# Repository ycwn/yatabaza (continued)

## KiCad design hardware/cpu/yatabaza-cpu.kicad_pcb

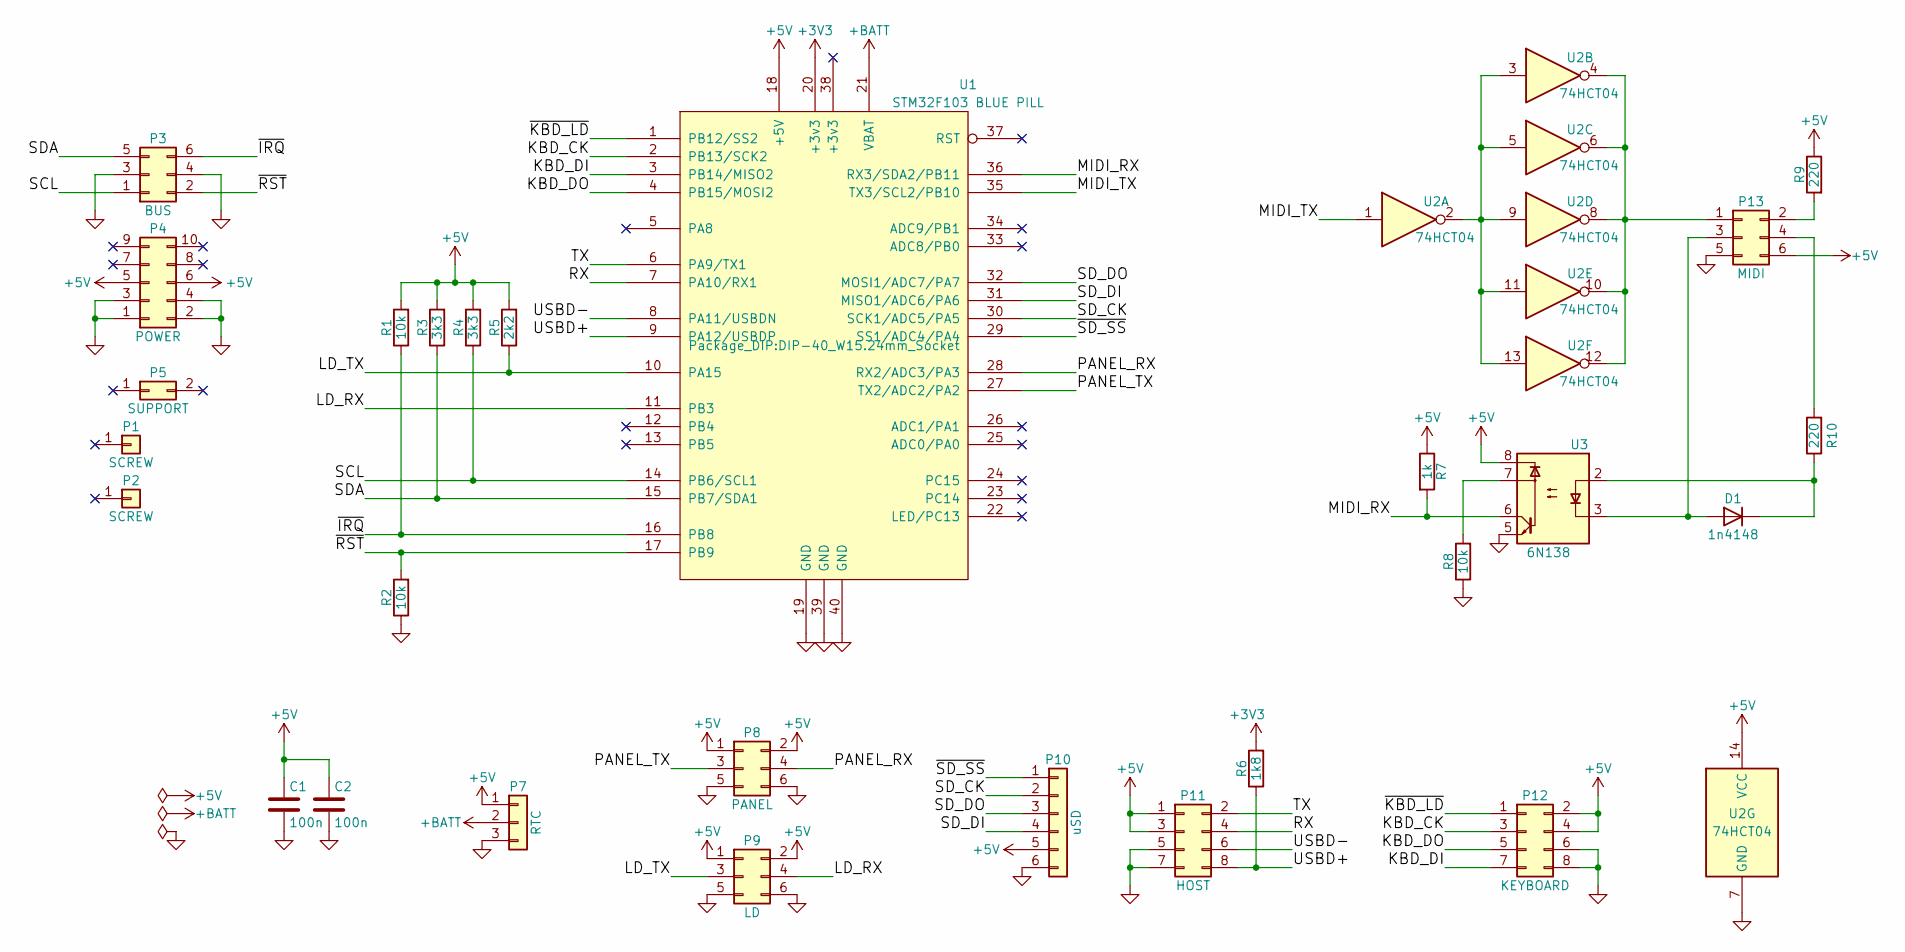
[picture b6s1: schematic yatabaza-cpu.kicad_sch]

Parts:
C1, C2: 100n; C_Disc_D3.0mm_W1.6mm_P2.50mm
D1: 1n4148; D_DO-35_SOD27_P2.54mm_Vertical_KathodeUp
P1, P2: SCREW; MountingHole_2.2mm_M2_ISO14580_Pad
P3: BUS; PinHeader_2x03_P2.54mm_Vertical
P4: POWER; PinHeader_2x05_P2.54mm_Vertical
P5: SUPPORT; PinHeader_1x02_P2.54mm_Vertical
P7: RTC; PinHeader_1x03_P2.54mm_Vertical
P8: PANEL; PinHeader_2x03_P2.54mm_Vertical
P9: LD; PinHeader_2x03_P2.54mm_Vertical
P10: uSD; PinHeader_1x06_P2.54mm_Vertical
P11: HOST; PinHeader_2x04_P2.54mm_Vertical
P12: KEYBOARD; PinHeader_2x04_P2.54mm_Horizontal
P13: MIDI; PinHeader_2x03_P2.54mm_Vertical
R1, R2, R8: 10k; R_Axial_DIN0204_L3.6mm_D1.6mm_P7.62mm_Horizontal
R3, R4: 3k3; R_Axial_DIN0204_L3.6mm_D1.6mm_P7.62mm_Horizontal
R5: 2k2; R_Axial_DIN0204_L3.6mm_D1.6mm_P2.54mm_Vertical
R6: 1k8; R_Axial_DIN0204_L3.6mm_D1.6mm_P7.62mm_Horizontal
R7: 1k; R_Axial_DIN0204_L3.6mm_D1.6mm_P7.62mm_Horizontal
R9, R10: 220; R_Axial_DIN0204_L3.6mm_D1.6mm_P2.54mm_Vertical
U1: STM32F103 BLUE PILL; DIP-40_W15.24mm_Socket
U2: 74HCT04; DIP-14_W7.62mm
U3: 6N138; DIP-8_W7.62mm

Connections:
+3V3: R6.2, U1.20 (+3v3)
+5V: C1.1, C2.1, P4.5, P4.6, P7.1, P8.1, P8.2, P9.1, P9.2, P10.5, P11.1, P11.3, P12.2, P12.4, P13.6, R1.2, R3.2, R4.2, R5.2, R7.1, R9.1, U1.18 (+5V), U2.14 (VCC), U3.8
+BATT: P7.2, U1.21 (VBAT)
/KBD_CK: P12.3, U1.2 (PB13/SCK2)
/KBD_DI: P12.7, U1.3 (PB14/MISO2)
/KBD_DO: P12.5, U1.4 (PB15/MOSI2)
/LD_RX: P9.4, U1.11 (PB3)
/LD_TX: P9.3, R5.1, U1.10 (PA15)
/MIDI_RX: R7.2, U1.36 (RX3/SDA2/PB11), U3.6
/MIDI_TX: U1.35 (TX3/SCL2/PB10), U2.1
/PANEL_RX: P8.4, U1.28 (RX2/ADC3/PA3)
/PANEL_TX: P8.3, U1.27 (TX2/ADC2/PA2)
/RX: P11.4, U1.7 (PA10/RX1)
/SCL: P3.1, R4.1, U1.14 (PB6/SCL1)
/SDA: P3.5, R3.1, U1.15 (PB7/SDA1)
/SD_CK: P10.2, U1.30 (SCK1/ADC5/PA5)
/SD_DI: P10.4, U1.31 (MISO1/ADC6/PA6)
/SD_DO: P10.3, U1.32 (MOSI1/ADC7/PA7)
/TX: P11.2, U1.6 (PA9/TX1)
/USBD+: P11.8, R6.1, U1.9 (PA12/USBDP)
/USBD-: P11.6, U1.8 (PA11/USBDN)
/~IRQ: P3.6, R1.1, U1.16 (PB8)
/~KBD_LD: P12.1, U1.1 (PB12/SS2)
/~RST: P3.2, R2.2, U1.17 (PB9)
/~SD_SS: P10.1, U1.29 (SS1/ADC4/PA4)
GND: C1.2, C2.2, P3.3, P3.4, P4.1, P4.2, P4.3, P4.4, P7.3, P8.5, P8.6, P9.5, P9.6, P10.6, P11.5, P11.7, P12.6, P12.8, P13.5, R2.1, R8.1, U1.19 (GND), U1.39 (GND), U1.40 (GND), U2.7 (GND), U3.5
unnamed: D1.1 (K), R10.1, U3.2
unnamed: D1.2 (A), P13.3, U3.3
unnamed: P13.1, U2.4, U2.6, U2.8, U2.10, U2.12
unnamed: P13.2, R9.2
unnamed: P13.4, R10.2
unnamed: R8.2, U3.7
unnamed: U2.2, U2.3, U2.5, U2.9, U2.11, U2.13

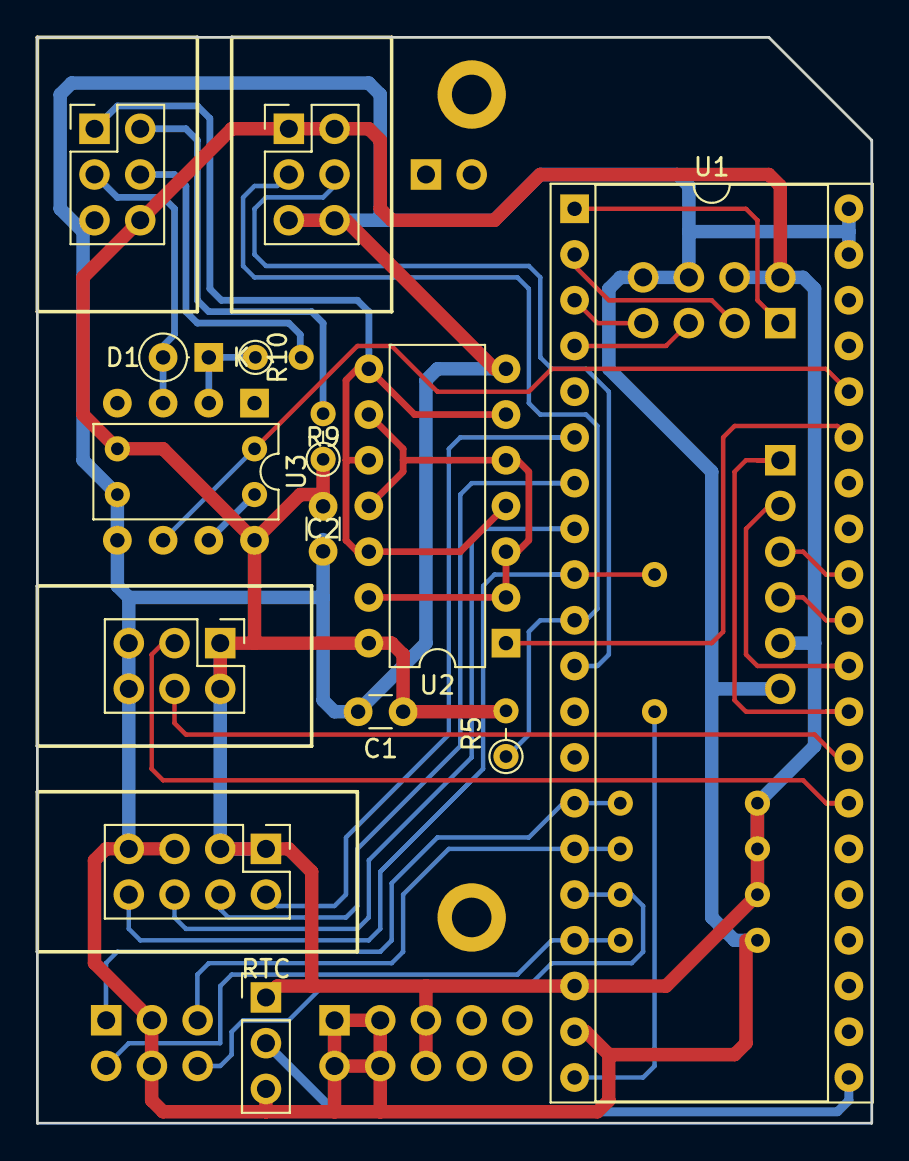
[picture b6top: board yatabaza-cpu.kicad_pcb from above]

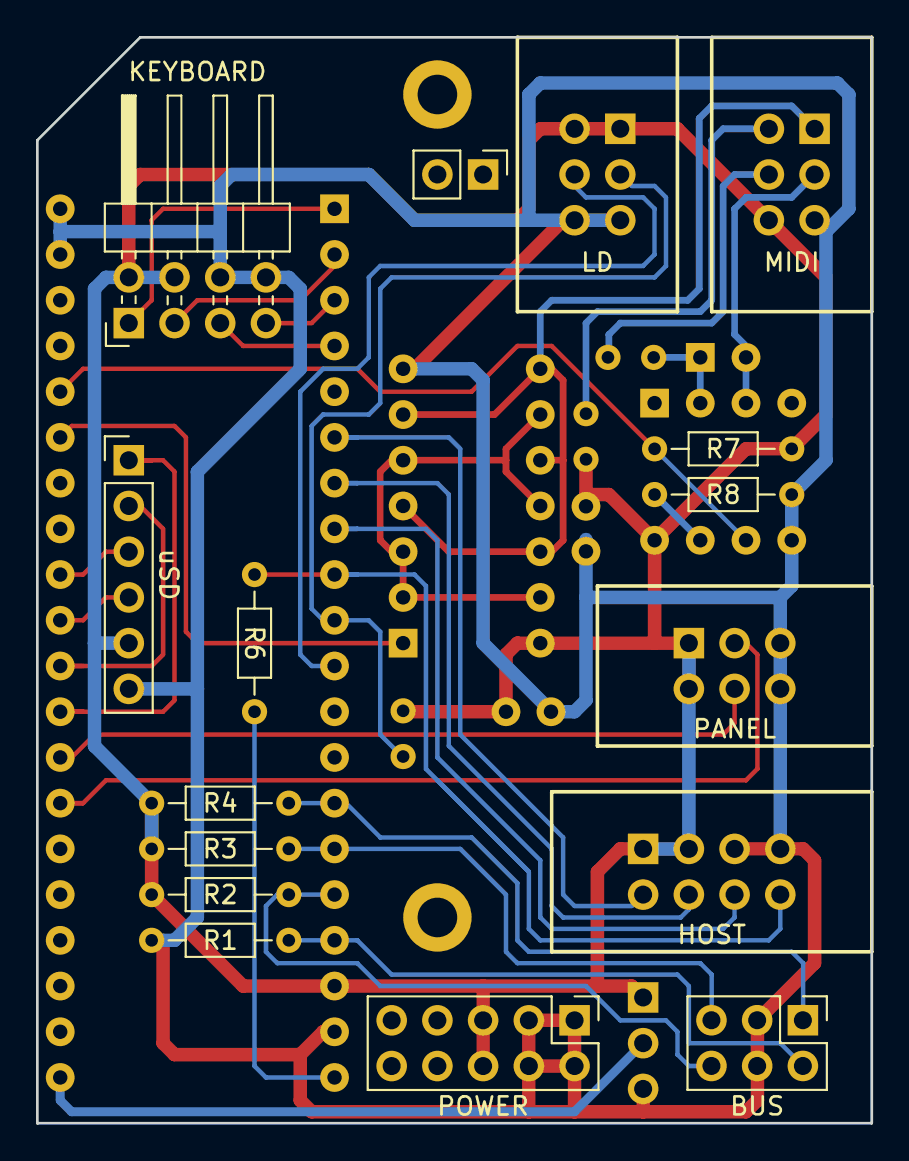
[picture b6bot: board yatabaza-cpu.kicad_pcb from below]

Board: 2 copper layers, 46.4 x 60.3 mm, 28 parts (12 on the bottom side), 33 nets.

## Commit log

2021-04-18 ~ Initial commit
2021-04-18 ~ Added schematic symbols
2021-04-18 ~ YM3812 Synthesizer board
2021-04-18 ~ STM32F103C8T6 CPU board
2021-04-18 ~ Main bus interconnect.
2021-04-18 ~ Power supply board.
2021-04-18 ~ XH-M228 power amplifier board.
2021-04-20 Create LICENSE
2021-04-20 ~ Main project
2021-04-20 ~ System console interface
2021-04-20 ~ Device interface
2021-04-20 ~ Loopback device
2021-04-20 ~ Service manager
2021-04-20 ~ CPU and peripheral governor service
2021-04-20 ~ System logger
2021-04-20 ~ Synth bus driver.
2021-04-20 ~ Synth bus scanner.
2021-04-29 ~ Code cleanup
2021-05-01 ~ Added documentation
2021-05-01 ~ Fixed flags passed to open() in creat() ~ Added the bus as dependency to the scanner service
2021-05-01 ~ Implemented OPL I/O core
2021-05-02 ~ Fixed header guards
2021-08-30 ~ Linked list container implementation.
2021-08-30 ~ Integrated FreeRTOS
2021-08-30 ~ FreeRTOS scheduler service
2021-08-30 ~ Minor cleanup
2021-08-30 ~ MIDI Core implementation
2021-08-31 ~ Added custom HAL configuration
2021-08-31 ~ Fixed invalid dependencies in scheduler
2021-09-02 ~ Fixed buggy MIDI event decoder
2021-09-02 ~ Added MIDI channel filter mask
2021-09-02 ~ Use a state-machine to track SysEx events
2021-09-02 ~ Implemented MIDI I/O device
2022-04-23 ~ Ported hardware to Kicad6
2022-04-23 ~ Added gerbers and schematics
2022-04-23 ~ Added datasheets for various components.
2022-04-23 ~ Added mechanical drawing of basic board
2022-05-02 ~ Added design for keyboard part
2022-05-03 ~ Change resistors to US style.
2022-05-11 ~ Implemented preprocessor magic.
2022-05-12 ~ Use preprocessor magic to simplify the service definitions.
2022-05-17 ~ Integrated FreeRTOS 202112.00, and got it to actually work now.
